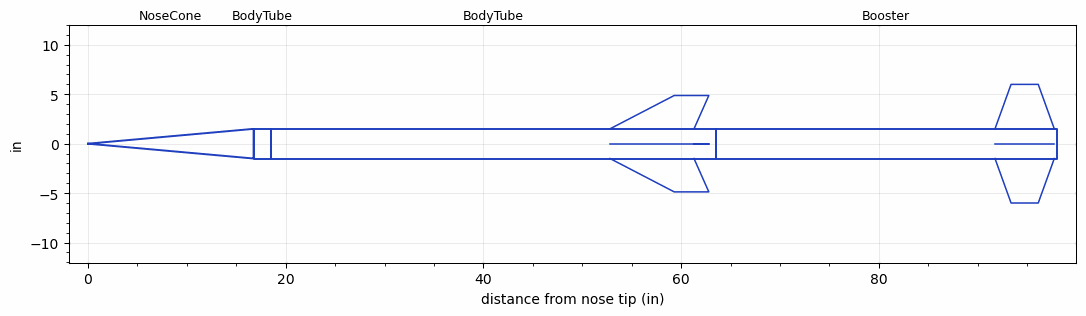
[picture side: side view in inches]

<RASAeroDocument>
 <FileVersion>2</FileVersion>
 <RocketDesign>
  <NoseCone>
   <Length>16.75</Length>
   <Diameter>3</Diameter>
   <Shape>Conical</Shape>
   <Location>0</Location>
  </NoseCone>
  <BodyTube>
   <Length>1.75</Length>
   <Diameter>3</Diameter>
   <Location>16.75</Location>
   <Protuberance>
    <StreamlinedNoBaseDrag>0</StreamlinedNoBaseDrag>
    <StreamlinedWithBaseDrag>0.44</StreamlinedWithBaseDrag>
    <InclinedPlate1Angle>0</InclinedPlate1Angle>
    <InclinedPlate1FrontalArea>0</InclinedPlate1FrontalArea>
    <InclinedPlate2Angle>0</InclinedPlate2Angle>
    <InclinedPlate2FrontalArea>0</InclinedPlate2FrontalArea>
   </Protuberance>
  </BodyTube>
  <BodyTube>
   <Length>45</Length>
   <Diameter>3</Diameter>
   <Location>18.5</Location>
   <Fin>
    <Count>4</Count>
    <Chord>8.5</Chord>
    <Span>3.375</Span>
    <SweepDistance>6.5</SweepDistance>
    <TipChord>3.5</TipChord>
    <Thickness>0.1875</Thickness>
    <LERadius>0.02</LERadius>
    <Location>10.7</Location>
    <AirfoilSection>Double Wedge</AirfoilSection>
    <FX1>1.75</FX1>
    <FX3>1.75</FX3>
   </Fin>
  </BodyTube>
  <Booster>
   <Length>34.5</Length>
   <Diameter>3</Diameter>
   <InsideDiameter>3</InsideDiameter>
   <RailGuideDiameter>0.7</RailGuideDiameter>
   <RailGuideHeight>0.5</RailGuideHeight>
   <Location>63.5</Location>
   <ShoulderLength>0</ShoulderLength>
   <Fin>
    <Count>4</Count>
    <Chord>6</Chord>
    <Span>4.5</Span>
    <SweepDistance>1.625</SweepDistance>
    <TipChord>2.75</TipChord>
    <Thickness>0.11</Thickness>
    <LERadius>0.01</LERadius>
    <Location>6.25</Location>
    <AirfoilSection>Hexagonal</AirfoilSection>
    <FX1>0.5</FX1>
    <FX3>0.5</FX3>
   </Fin>
  </Booster>
  <Surface>Rough Camouflage Paint</Surface>
  <ModifiedBarrowman>True</ModifiedBarrowman>
  <Turbulence>True</Turbulence>
  <UseBooster1>False</UseBooster1>
  <UseBooster2>False</UseBooster2>
 </RocketDesign>
 <LaunchSite>
  <Altitude>2400</Altitude>
  <Pressure>0</Pressure>
  <RodAngle>2</RodAngle>
  <RodLength>15</RodLength>
  <Temperature>30</Temperature>
  <WindSpeed>5</WindSpeed>
 </LaunchSite>
 <Recovery>
  <Altitude1>1000</Altitude1>
  <Altitude2>1000</Altitude2>
  <DeviceType1>Parachute</DeviceType1>
  <DeviceType2>Parachute</DeviceType2>
  <Event1>False</Event1>
  <Event2>False</Event2>
  <Size1>9</Size1>
  <Size2>36</Size2>
  <EventType1>Apogee</EventType1>
  <EventType2>Altitude</EventType2>
  <CD1>0.75</CD1>
  <CD2>2</CD2>
 </Recovery>
 <SimulationList>
  <Simulation>
   <SustainerEngine>M1850Real  (NotAerotech)</SustainerEngine>
   <SustainerLaunchWt>21</SustainerLaunchWt>
   <SustainerNozzleDiameter>2.9</SustainerNozzleDiameter>
   <SustainerCG>36.4</SustainerCG>
   <SustainerIgnitionDelay>6</SustainerIgnitionDelay>
   <Booster1Engine>M2051X  (NotAeroTech)</Booster1Engine>
   <Booster1LaunchWt>34</Booster1LaunchWt>
   <Booster1SeparationDelay>0</Booster1SeparationDelay>
   <Booster1IgnitionDelay>0</Booster1IgnitionDelay>
   <Booster1CG>53.6</Booster1CG>
   <Booster1NozzleDiameter>2.9</Booster1NozzleDiameter>
   <IncludeBooster1>True</IncludeBooster1>
   <Booster2Delay>0</Booster2Delay>
   <IncludeBooster2>False</IncludeBooster2>
   <TimetoApogee>69.12576</TimetoApogee>
   <MaxAltitude>80467.9</MaxAltitude>
   <MaxVelocity>3594.023</MaxVelocity>
  </Simulation>
 </SimulationList>
</RASAeroDocument>
